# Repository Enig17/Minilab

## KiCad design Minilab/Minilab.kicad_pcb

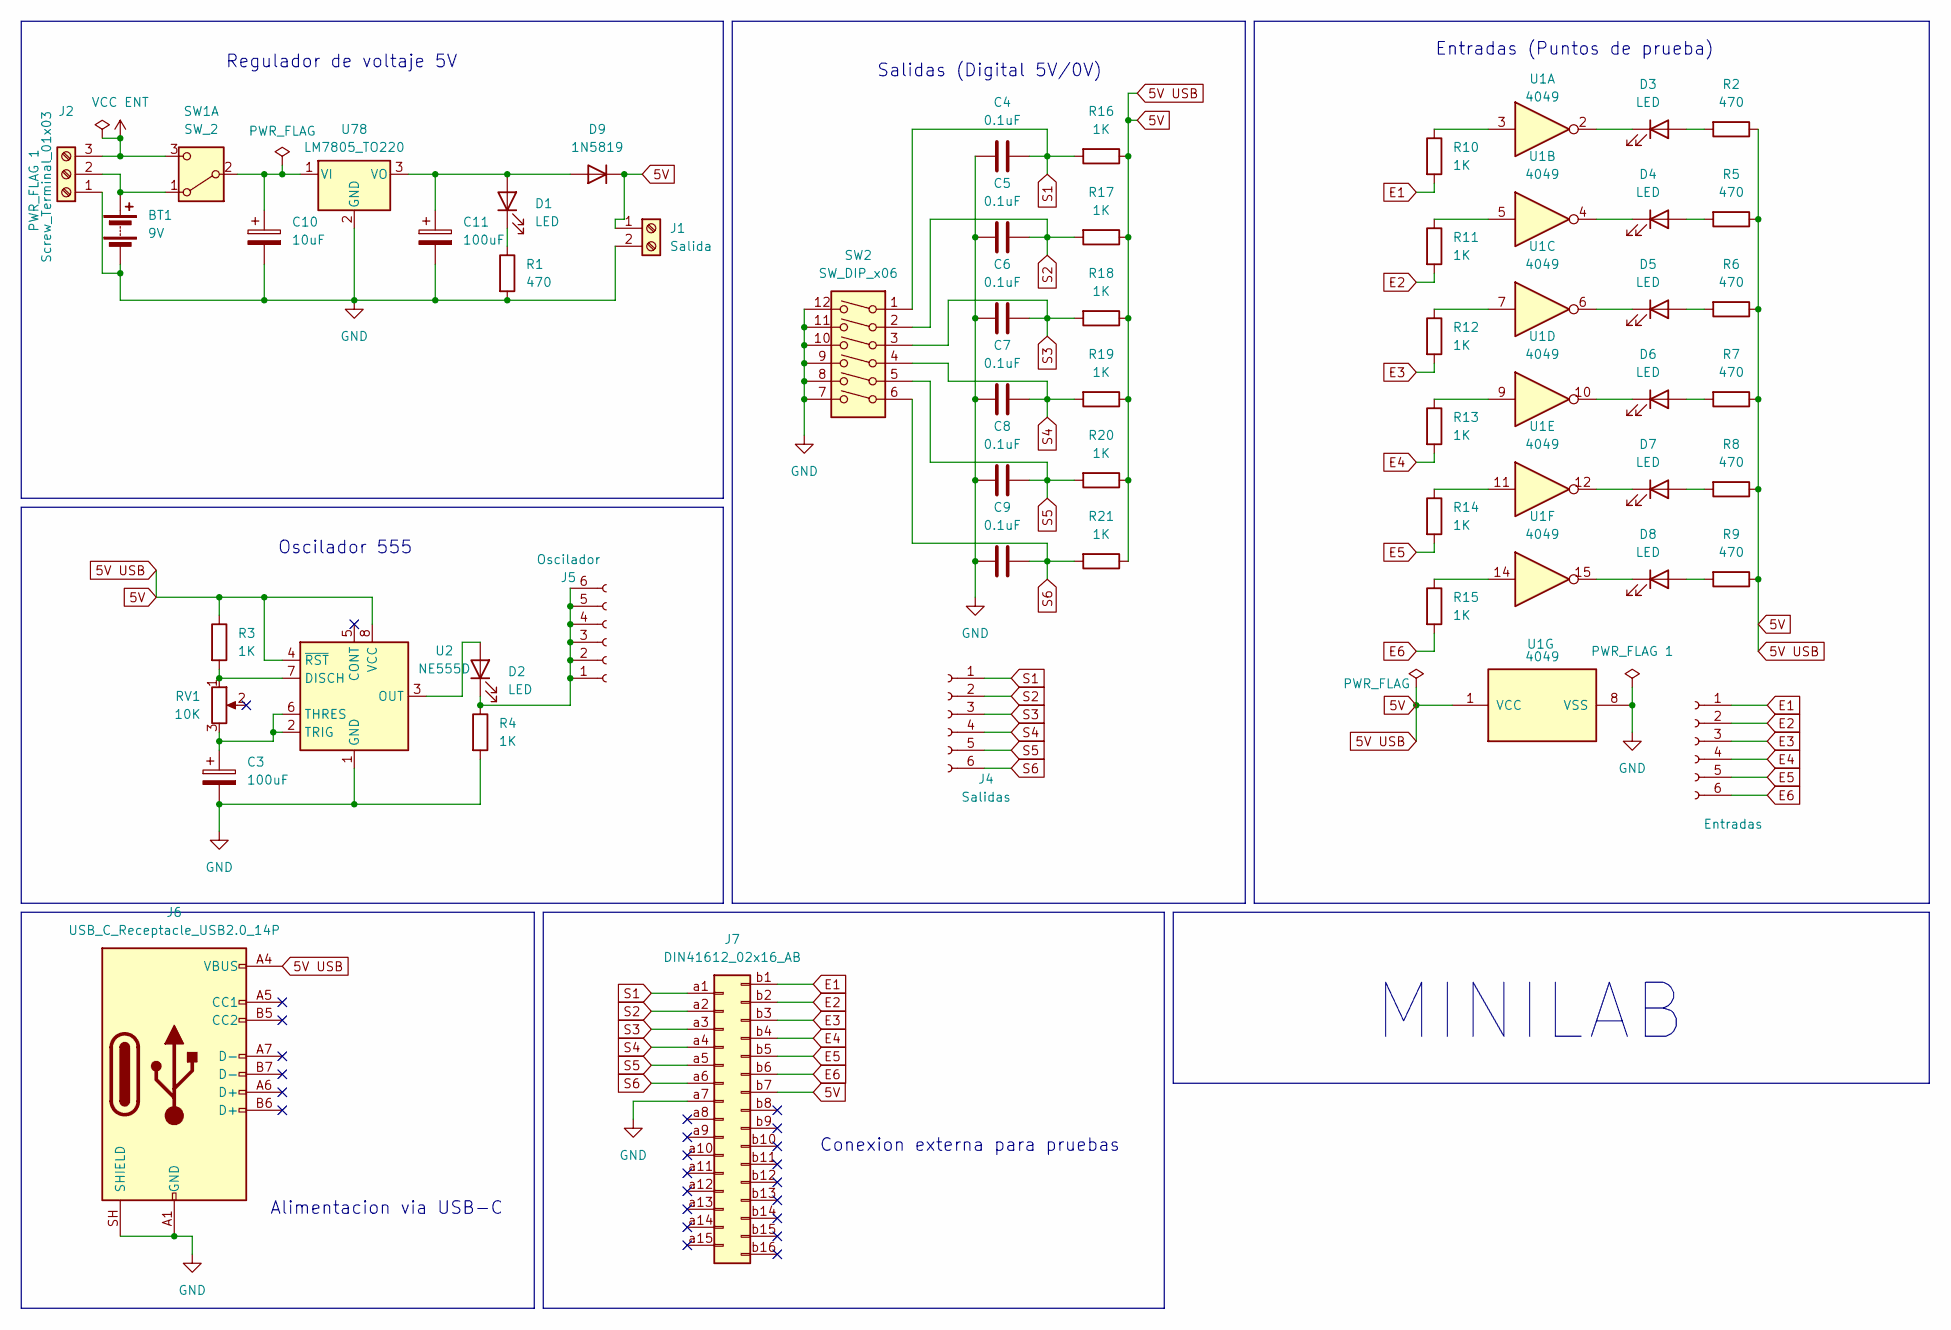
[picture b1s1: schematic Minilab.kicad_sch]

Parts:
BT1: 9V
C3, C11: 100uF; CP_Radial_D5.0mm_P2.50mm
C4, C5, C6, C7, C8, C9: 0.1uF; C_Disc_D5.0mm_W2.5mm_P5.00mm
C10: 10uF; CP_Radial_D5.0mm_P2.50mm
D1, D2, D3, D4, D5, D6, D7, D8: LED; LED_D5.0mm
D9: 1N5819; D_DO-41_SOD81_P10.16mm_Horizontal
J1: Salida; TerminalBlock_MaiXu_MX126-5.0-02P_1x02_P5.00mm
J2: Screw_Terminal_01x03; TerminalBlock_MaiXu_MX126-5.0-03P_1x03_P5.00mm
J3: Entradas; PinSocket_1x06_P2.54mm_Vertical
J4: Salidas; PinSocket_1x06_P2.54mm_Vertical
J5: Oscilador; PinSocket_1x06_P2.54mm_Vertical
J6: USB_C_Receptacle_USB2.0_14P; USB_C_Receptacle_GCT_USB4125-xx-x_6P_TopMnt_Horizontal
J7: DIN41612_02x16_AB; DIN41612_B_2x16_Female_Vertical_THT
R1, R2, R5, R6, R7, R8, R9: 470; R_Axial_DIN0204_L3.6mm_D1.6mm_P2.54mm_Vertical
R3, R4, R10, R11, R12, R13, R14, R15, R16, R17, R18, R19, R20, R21: 1K; R_Axial_DIN0204_L3.6mm_D1.6mm_P2.54mm_Vertical
RV1: 10K; Potentiometer_Piher_PC-16_Single_Horizontal
SW1: SW_2
SW2: SW_DIP_x06; SW_DIP_SPSTx06_Slide_6.7x16.8mm_W7.62mm_P2.54mm_LowProfile
U1: 4049; CERDIP-16_W7.62mm_SideBrazed
U2: NE555D; DIP-8_W7.62mm
U78: LM7805_TO220; TO-220-3_Vertical

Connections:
5V: D9.1 (K), J1.1, J6.A4 (VBUS), J6.A9 (VBUS), J6.B4 (VBUS), J6.B9 (VBUS), J7.b6 (Pin_b14_b14), J7.b7, R2.1, R3.1, R5.1, R6.1, R7.1, R8.1, R9.1, R16.1, R17.1, R18.1, R19.1, R20.1, R21.1, U1.1 (VCC), U2.4 (~RST), U2.8 (VCC)
E1: J3.1, J7.b1 (Pin_b2_b2), R10.2
E2: J3.2, J7.b2 (Pin_b4_b4), R11.2
E3: J3.3, J7.b3 (Pin_b6_b6), R12.2
E4: J3.4, J7.b4 (Pin_b8_b8), R13.2
E5: J3.5, J7.b5 (Pin_b10_b10), R14.2
E6: J3.6, J7.b6 (Pin_b12_b12), R15.2
GND: BT1.2 (-), C3.2, C4.2, C5.2, C6.2, C7.2, C8.2, C9.2, C10.2, C11.2, J1.2, J2.1, J6.A1 (GND), J6.A12 (GND), J6.B1 (GND), J6.B12 (GND), J6.SH (SHIELD), J7.a7 (Pin_a14_a14), R1.2, R4.2, SW2.7, SW2.8, SW2.9, SW2.10, SW2.11, SW2.12, U1.8 (VSS), U2.1 (GND), U78.2 (GND)
unnamed: C11.1, D1.2 (A), D9.2 (A), U78.3 (VO)
unnamed: D1.1 (K), R1.1
unnamed: D2.2 (A), U2.3 (OUT)
unnamed: D2.1 (K), J5.1, J5.2, J5.3, J5.4, J5.5, J5.6, R4.1
unnamed: D3.2 (A), R2.2
unnamed: D3.1 (K), U1.2
unnamed: D4.2 (A), R5.2
unnamed: D4.1 (K), U1.4
unnamed: D5.2 (A), R6.2
unnamed: D5.1 (K), U1.6
unnamed: D6.2 (A), R7.2
unnamed: D6.1 (K), U1.10
unnamed: D7.2 (A), R8.2
unnamed: D7.1 (K), U1.12
unnamed: D8.2 (A), R9.2
unnamed: D8.1 (K), U1.15
unnamed: BT1.1 (+), J2.2, SW1.1 (A)
unnamed: R10.1, U1.3
unnamed: R11.1, U1.5
unnamed: R12.1, U1.7
unnamed: R13.1, U1.9
unnamed: R14.1, U1.11
unnamed: R15.1, U1.14
unnamed: R3.2, RV1.1, U2.7 (DISCH)
unnamed: C3.1, RV1.3, U2.2 (TRIG), U2.6 (THRES)
unnamed: C10.1, SW1.2 (B), U78.1 (VI)
S1: C4.1, J4.1, J7.a1 (Pin_a2_a2), R16.2, SW2.1
S2: C5.1, J4.2, J7.a2 (Pin_a4_a4), R17.2, SW2.2
S3: C6.1, J4.3, J7.a3 (Pin_a6_a6), R18.2, SW2.3
S4: C7.1, J4.4, J7.a4 (Pin_a8_a8), R19.2, SW2.4
S5: C8.1, J4.5, J7.a5 (Pin_a10_a10), R20.2, SW2.5
S6: C9.1, J4.6, J7.a6 (Pin_a12_a12), R21.2, SW2.6
VCC ENT: J2.3, SW1.3 (C)

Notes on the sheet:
Conexion externa para pruebas
Oscilador 555
Alimentacion via USB-C
MINILAB
Salidas (Digital 5V/0V)
Entradas (Puntos de prueba)
Regulador de voltaje 5V

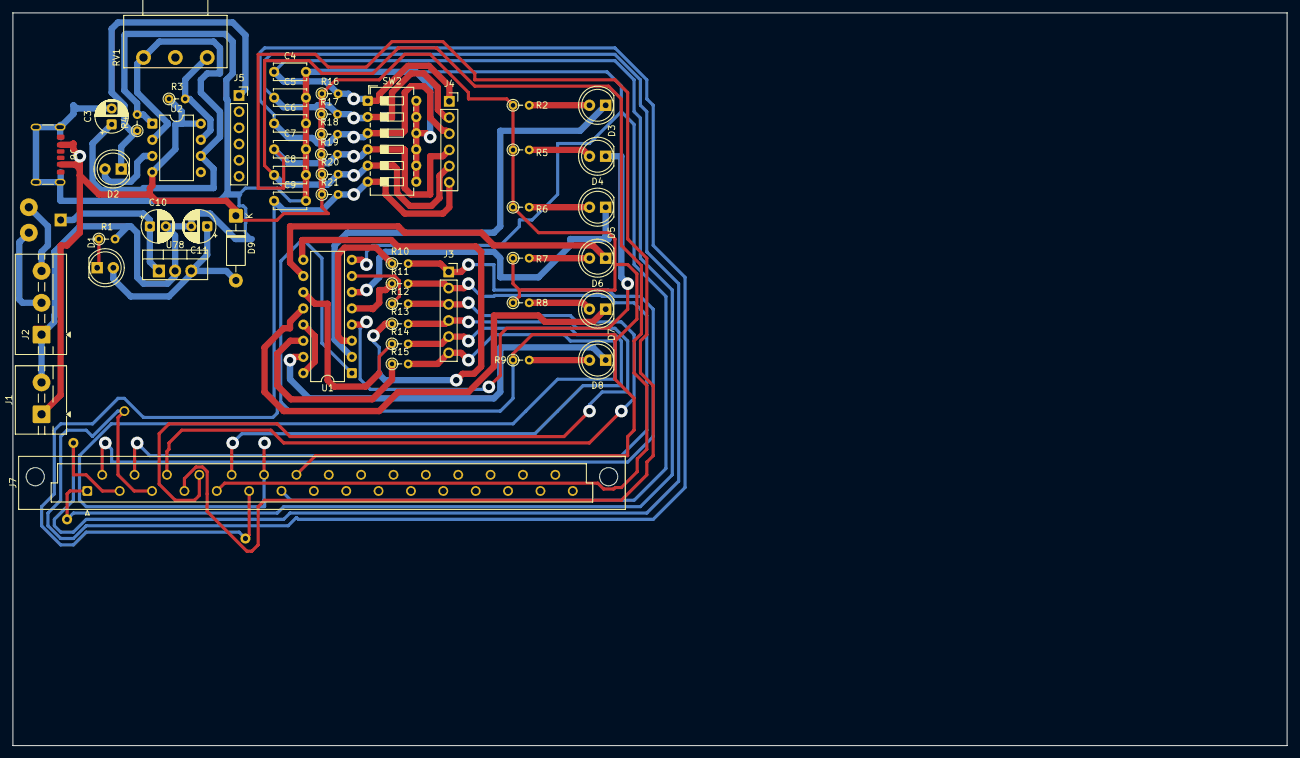
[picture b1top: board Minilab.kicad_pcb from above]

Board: 2 copper layers, 200.0 x 115.0 mm, 51 parts (0 on the bottom side), 39 nets.

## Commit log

2026-04-25 Primer commit
2026-05-13 Actualizacion3
2026-05-13 Actualizacion4
2026-05-13 Actualizacion5
2026-05-13 Actualizacion6
2026-05-13 Add image to README.md
